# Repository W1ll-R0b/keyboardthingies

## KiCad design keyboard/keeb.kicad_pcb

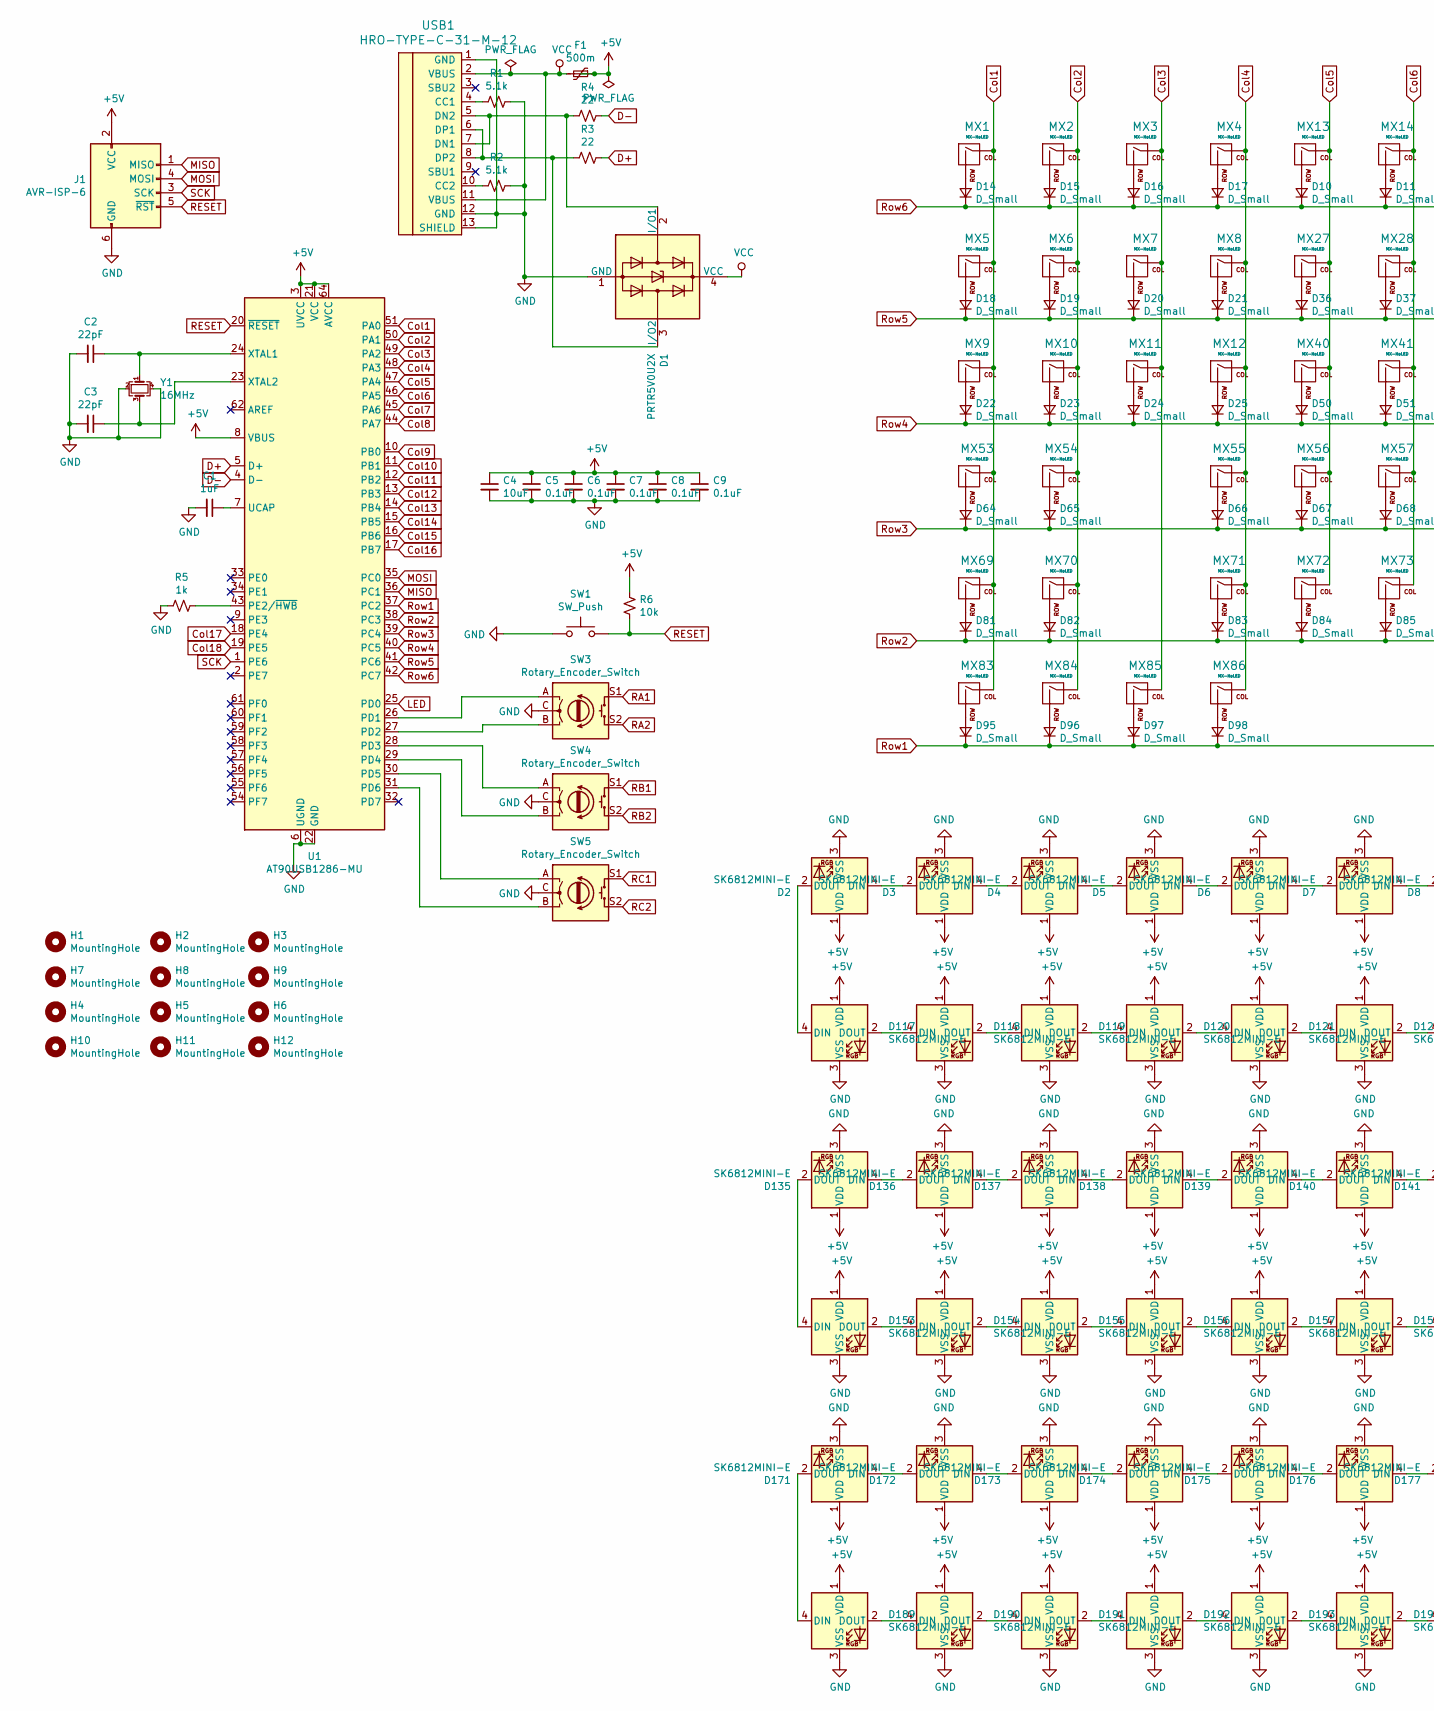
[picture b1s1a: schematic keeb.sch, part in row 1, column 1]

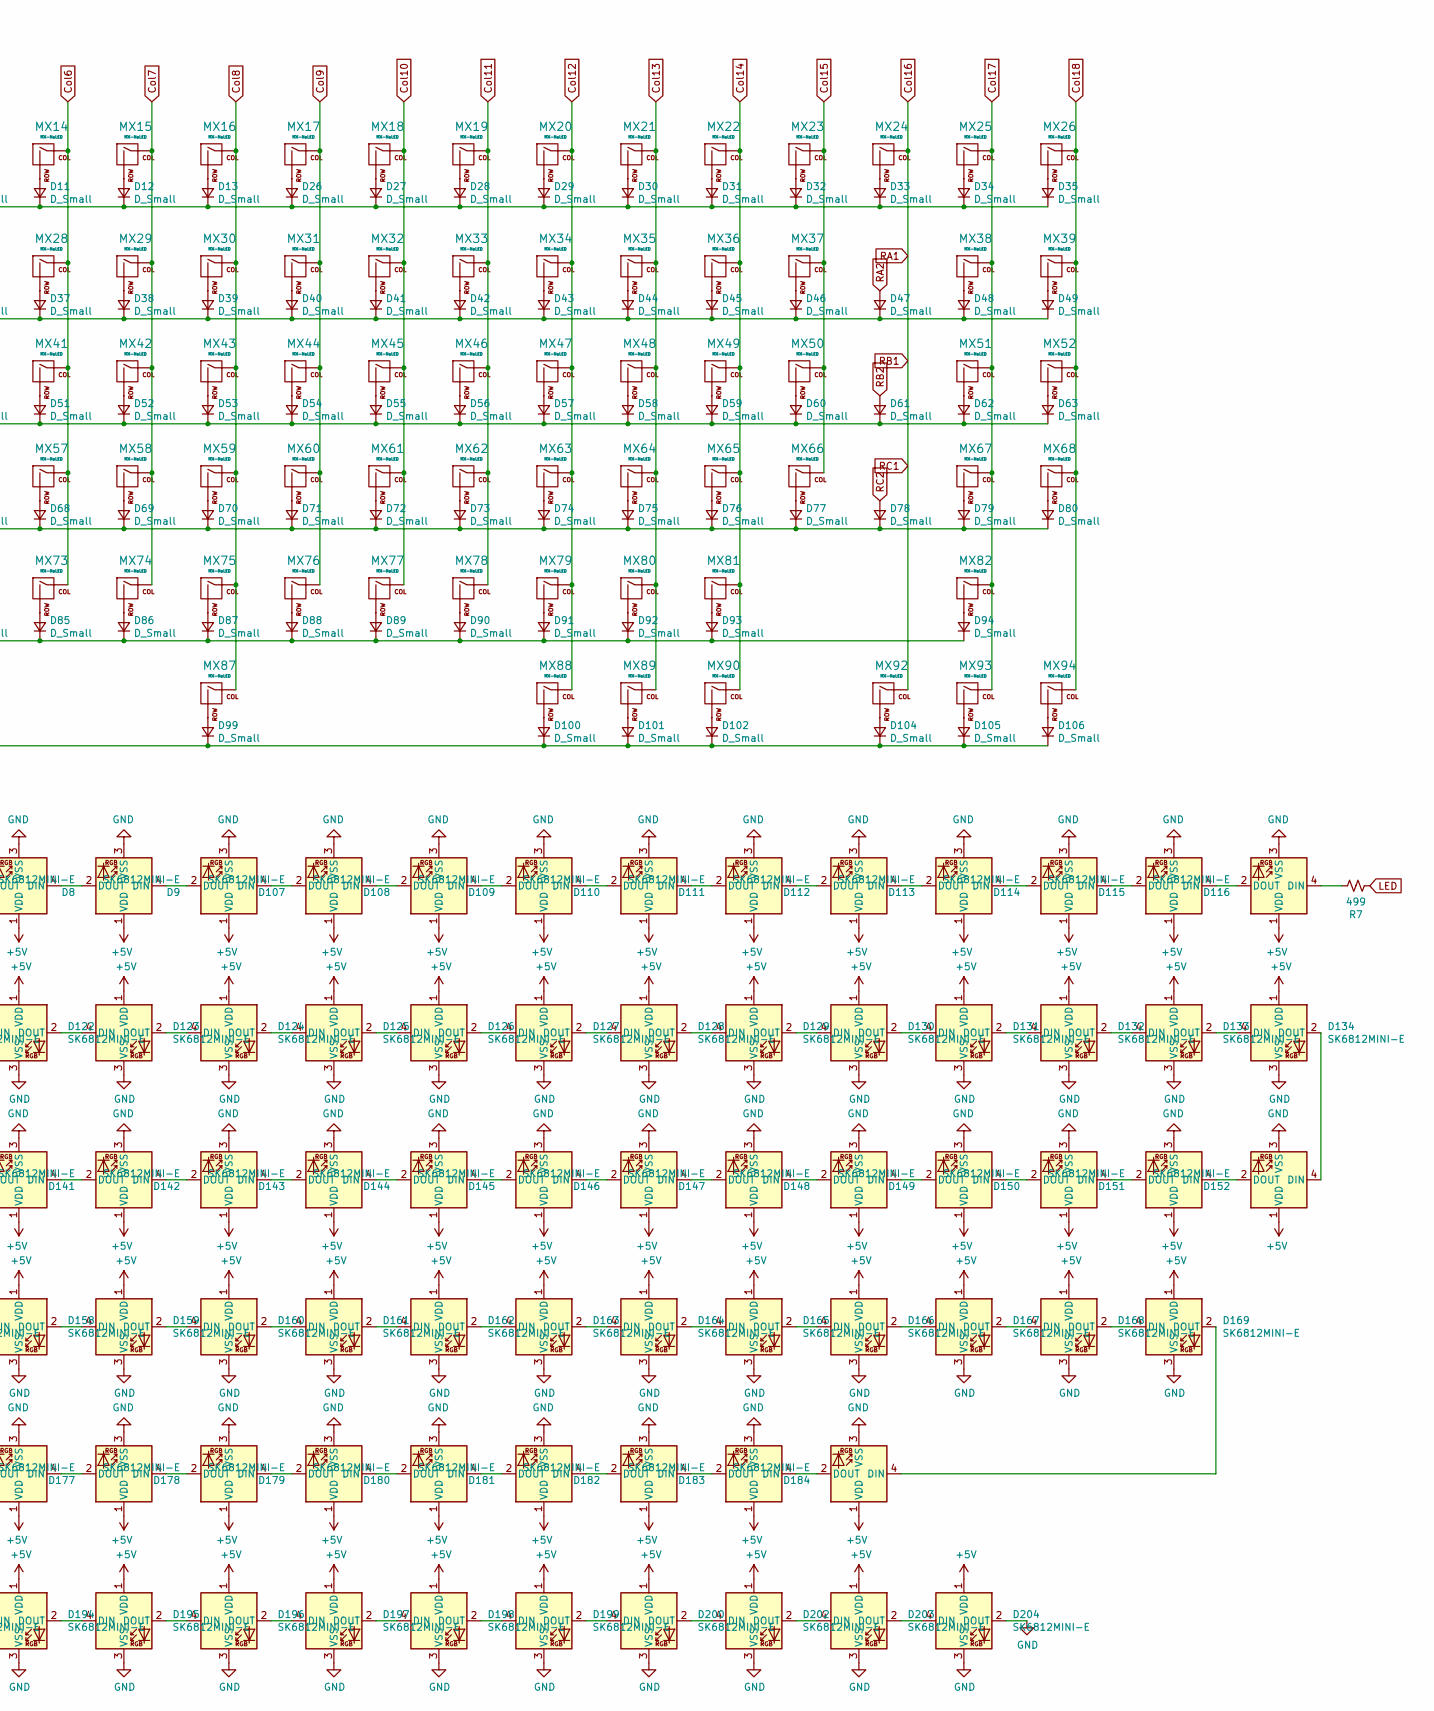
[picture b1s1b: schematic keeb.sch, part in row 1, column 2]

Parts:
C1: 1uF; C_0805_2012Metric
C2, C3: 22pF; C_0805_2012Metric
C4: 10uF; C_0805_2012Metric
C5, C6, C7, C8, C9: 0.1uF; C_0805_2012Metric
D1: PRTR5V0U2X; SOT-143
D2, D3, D4, D5, D6, D7, D8, D9, D107, D108, D109, D110, D111, D112, D113, D114, D115, D116, D117, D118, D119, D120, D121, D122, D123, D124, D125, D126, D127, D128, D129, D130, D131, D132, D133, D134, D135, D136, D137, D138, D139, D140, D141, D142, D143, D144, D145, D146, D147, D148, D149, D150, D151, D152, D153, D154, D155, D156, D157, D158, D159, D160, D161, D162, D163, D164, D165, D166, D167, D168, D169, D171, D172, D173, D174, D175, D176, D177, D178, D179, D180, D181, D182, D183, D184, D189, D190, D191, D192, D193, D194, D195, D196, D197, D198, D199, D200, D202, D203, D204: SK6812MINI-E; MX_SK6812MINI-E
D10, D11, D12, D13, D14, D15, D16, D17, D18, D19, D20, D21, D22, D23, D24, D25, D26, D27, D28, D29, D30, D31, D32, D33, D34, D35, D36, D37, D38, D39, D40, D41, D42, D43, D44, D45, D46, D47, D48, D49, D50, D51, D52, D53, D54, D55, D56, D57, D58, D59, D60, D61, D62, D63, D64, D65, D66, D67, D68, D69, D70, D71, D72, D73, D74, D75, D76, D77, D78, D79, D80, D81, D82, D83, D84, D85, D86, D87, D88, D89, D90, D91, D92, D93, D94, D95, D96, D97, D98, D99, D100, D101, D102, D104, D105, D106: D_Small; D_SOD-123
F1: 500m; Fuse_1206_3216Metric_Pad1.42x1.75mm_HandSolder
H1, H2, H3, H4, H5, H6, H7, H8, H9, H10, H11, H12: MountingHole; MountingHole_2.2mm_M2_DIN965_Pad
J1: AVR-ISP-6; Reset_Pretty-Mask
MX1, MX2, MX3, MX4, MX5, MX6, MX7, MX8, MX9, MX11, MX12, MX13, MX14, MX15, MX16, MX17, MX18, MX19, MX20, MX21, MX22, MX23, MX24, MX25, MX26, MX27, MX28, MX29, MX30, MX31, MX32, MX33, MX34, MX35, MX36, MX38, MX39, MX40, MX41, MX42, MX43, MX44, MX45, MX46, MX47, MX48, MX49, MX51, MX52, MX53, MX55, MX56, MX57, MX58, MX59, MX60, MX61, MX62, MX63, MX64, MX65, MX67, MX68, MX69, MX71, MX72, MX73, MX74, MX75, MX76, MX77, MX78, MX79, MX80, MX82, MX83, MX92, MX93, MX94: MX-NoLED; MXOnly-1U-NoLED
MX10, MX50: MX-NoLED; MXOnly-1.5U-NoLED
MX37: MX-NoLED; MXOnly-2U-NoLED
MX54: MX-NoLED; MXOnly-1.75U-NoLED
MX66, MX70: MX-NoLED; MXOnly-2.25U-NoLED
MX81: MX-NoLED; MXOnly-2.75U-NoLED
MX84, MX85, MX86, MX88, MX89, MX90: MX-NoLED; MXOnly-1.25U-NoLED
MX87: MX-NoLED; MXOnly-6.25U-NoLED
R1, R2: 5.1k; R_0805_2012Metric
R3, R4: 22; R_0805_2012Metric
R5: 1k; R_0805_2012Metric
R6: 10k; R_0805_2012Metric
R7: 499; R_0805_2012Metric
SW1: SW_Push; SKQG-1155865
SW3, SW4, SW5: Rotary_Encoder_Switch; RotaryEncoder_Alps_EC11E-Switch_Vertical_H20mm
U1: AT90USB1286-MU; QFN-64-1EP_9x9mm_P0.5mm_EP7.5x7.5mm
USB1: HRO-TYPE-C-31-M-12; HRO-TYPE-C-31-M-12-HandSoldering
Y1: 16MHz; Crystal_SMD_3225-4Pin_3.2x2.5mm

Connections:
+5V: C4.1, C5.1, C6.1, C7.1, C8.1, C9.1, D2.1 (VDD), D3.1 (VDD), D4.1 (VDD), D5.1 (VDD), D6.1 (VDD), D7.1 (VDD), D8.1 (VDD), D9.1 (VDD), D107.1 (VDD), D108.1 (VDD), D109.1 (VDD), D110.1 (VDD), D111.1 (VDD), D112.1 (VDD), D113.1 (VDD), D114.1 (VDD), D115.1 (VDD), D116.1 (VDD), D117.1 (VDD), D118.1 (VDD), D119.1 (VDD), D120.1 (VDD), D121.1 (VDD), D122.1 (VDD), D123.1 (VDD), D124.1 (VDD), D125.1 (VDD), D126.1 (VDD), D127.1 (VDD), D128.1 (VDD), D129.1 (VDD), D130.1 (VDD), D131.1 (VDD), D132.1 (VDD), D133.1 (VDD), D134.1 (VDD), D135.1 (VDD), D136.1 (VDD), D137.1 (VDD), D138.1 (VDD), D139.1 (VDD), D140.1 (VDD), D141.1 (VDD), D142.1 (VDD), D143.1 (VDD), D144.1 (VDD), D145.1 (VDD), D146.1 (VDD), D147.1 (VDD), D148.1 (VDD), D149.1 (VDD), D150.1 (VDD), D151.1 (VDD), D152.1 (VDD), D153.1 (VDD), D154.1 (VDD), D155.1 (VDD), D156.1 (VDD), D157.1 (VDD), D158.1 (VDD), D159.1 (VDD), D160.1 (VDD), D161.1 (VDD), D162.1 (VDD), D163.1 (VDD), D164.1 (VDD), D165.1 (VDD), D166.1 (VDD), D167.1 (VDD), D168.1 (VDD), D169.1 (VDD), D171.1 (VDD), D172.1 (VDD), D173.1 (VDD), D174.1 (VDD), D175.1 (VDD), D176.1 (VDD), D177.1 (VDD), D178.1 (VDD), D179.1 (VDD), D180.1 (VDD), D181.1 (VDD), D182.1 (VDD), D183.1 (VDD), D184.1 (VDD), D189.1 (VDD), D190.1 (VDD), D191.1 (VDD), D192.1 (VDD), D193.1 (VDD), D194.1 (VDD), D195.1 (VDD), D196.1 (VDD), D197.1 (VDD), D198.1 (VDD), D199.1 (VDD), D200.1 (VDD), D202.1 (VDD), D203.1 (VDD), D204.1 (VDD), F1.1, J1.2 (VCC), R6.1, U1.3 (UVCC), U1.8 (VBUS), U1.21 (VCC), U1.52 (VCC), U1.64 (AVCC)
Col1: MX1.1 (COL), MX5.1 (COL), MX9.1 (COL), MX53.1 (COL), MX69.1 (COL), MX83.1 (COL), U1.51 (PA0)
Col2: MX2.1 (COL), MX6.1 (COL), MX10.1 (COL), MX54.1 (COL), MX70.1 (COL), MX84.1 (COL), U1.50 (PA1)
Col3: MX3.1 (COL), MX7.1 (COL), MX11.1 (COL), MX85.1 (COL), U1.49 (PA2)
Col4: MX4.1 (COL), MX8.1 (COL), MX12.1 (COL), MX55.1 (COL), MX71.1 (COL), MX86.1 (COL), U1.48 (PA3)
Col5: MX13.1 (COL), MX27.1 (COL), MX40.1 (COL), MX56.1 (COL), MX72.1 (COL), U1.47 (PA4)
Col6: MX14.1 (COL), MX28.1 (COL), MX41.1 (COL), MX57.1 (COL), MX73.1 (COL), U1.46 (PA5)
Col7: MX15.1 (COL), MX29.1 (COL), MX42.1 (COL), MX58.1 (COL), MX74.1 (COL), U1.45 (PA6)
Col8: MX16.1 (COL), MX30.1 (COL), MX43.1 (COL), MX59.1 (COL), MX75.1 (COL), MX87.1 (COL), U1.44 (PA7)
Col9: MX17.1 (COL), MX31.1 (COL), MX44.1 (COL), MX60.1 (COL), MX76.1 (COL), U1.10 (PB0)
Col10: MX18.1 (COL), MX32.1 (COL), MX45.1 (COL), MX61.1 (COL), MX77.1 (COL), U1.11 (PB1)
Col11: MX19.1 (COL), MX33.1 (COL), MX46.1 (COL), MX62.1 (COL), MX78.1 (COL), U1.12 (PB2)
Col12: MX20.1 (COL), MX34.1 (COL), MX47.1 (COL), MX63.1 (COL), MX79.1 (COL), MX88.1 (COL), U1.13 (PB3)
Col13: MX21.1 (COL), MX35.1 (COL), MX48.1 (COL), MX64.1 (COL), MX80.1 (COL), MX89.1 (COL), U1.14 (PB4)
Col14: MX22.1 (COL), MX36.1 (COL), MX49.1 (COL), MX65.1 (COL), MX81.1 (COL), MX90.1 (COL), U1.15 (PB5)
Col15: MX23.1 (COL), MX37.1 (COL), MX50.1 (COL), MX66.1 (COL), U1.16 (PB6)
Col16: MX24.1 (COL), MX92.1 (COL), SW3.S1, SW4.S1, SW5.S1, U1.17 (PB7)
Col17: MX25.1 (COL), MX38.1 (COL), MX51.1 (COL), MX67.1 (COL), MX82.1 (COL), MX93.1 (COL), U1.18 (PE4)
Col18: MX26.1 (COL), MX39.1 (COL), MX52.1 (COL), MX68.1 (COL), MX94.1 (COL), U1.19 (PE5)
D+: R3.1, U1.5 (D+)
D-: R4.1, U1.4 (D-)
GND: C1.2, C2.2, C3.2, C4.2, C5.2, C6.2, C7.2, C8.2, C9.2, D1.1 (GND), D2.3 (VSS), D3.3 (VSS), D4.3 (VSS), D5.3 (VSS), D6.3 (VSS), D7.3 (VSS), D8.3 (VSS), D9.3 (VSS), D107.3 (VSS), D108.3 (VSS), D109.3 (VSS), D110.3 (VSS), D111.3 (VSS), D112.3 (VSS), D113.3 (VSS), D114.3 (VSS), D115.3 (VSS), D116.3 (VSS), D117.3 (VSS), D118.3 (VSS), D119.3 (VSS), D120.3 (VSS), D121.3 (VSS), D122.3 (VSS), D123.3 (VSS), D124.3 (VSS), D125.3 (VSS), D126.3 (VSS), D127.3 (VSS), D128.3 (VSS), D129.3 (VSS), D130.3 (VSS), D131.3 (VSS), D132.3 (VSS), D133.3 (VSS), D134.3 (VSS), D135.3 (VSS), D136.3 (VSS), D137.3 (VSS), D138.3 (VSS), D139.3 (VSS), D140.3 (VSS), D141.3 (VSS), D142.3 (VSS), D143.3 (VSS), D144.3 (VSS), D145.3 (VSS), D146.3 (VSS), D147.3 (VSS), D148.3 (VSS), D149.3 (VSS), D150.3 (VSS), D151.3 (VSS), D152.3 (VSS), D153.3 (VSS), D154.3 (VSS), D155.3 (VSS), D156.3 (VSS), D157.3 (VSS), D158.3 (VSS), D159.3 (VSS), D160.3 (VSS), D161.3 (VSS), D162.3 (VSS), D163.3 (VSS), D164.3 (VSS), D165.3 (VSS), D166.3 (VSS), D167.3 (VSS), D168.3 (VSS), D169.3 (VSS), D171.3 (VSS), D172.3 (VSS), D173.3 (VSS), D174.3 (VSS), D175.3 (VSS), D176.3 (VSS), D177.3 (VSS), D178.3 (VSS), D179.3 (VSS), D180.3 (VSS), D181.3 (VSS), D182.3 (VSS), D183.3 (VSS), D184.3 (VSS), D189.3 (VSS), D190.3 (VSS), D191.3 (VSS), D192.3 (VSS), D193.3 (VSS), D194.3 (VSS), D195.3 (VSS), D196.3 (VSS), D197.3 (VSS), D198.3 (VSS), D199.3 (VSS), D200.3 (VSS), D202.3 (VSS), D203.3 (VSS), D204.2 (DOUT), D204.3 (VSS), H1.1, H2.1, H3.1, H4.1, H5.1, H6.1, H7.1, H8.1, H9.1, H10.1, H11.1, H12.1, J1.6 (GND), R1.1, R2.1, R5.2, SW1.1, SW3.C, SW4.C, SW5.C, U1.6 (UGND), U1.22 (GND), U1.53 (GND), U1.63 (GND), U1.65 (GND), USB1.1 (GND), USB1.12 (GND), USB1.13 (SHIELD), Y1.2, Y1.4
LED: R7.2, U1.25 (PD0)
MISO: J1.1 (MISO), U1.36 (PC1)
MOSI: J1.4 (MOSI), U1.35 (PC0)
unnamed: C1.1, U1.7 (UCAP)
unnamed: C2.1, U1.24 (XTAL1), Y1.1
unnamed: C3.1, U1.23 (XTAL2), Y1.3
unnamed: D1.2 (I/O1), R4.2, USB1.5 (DN2), USB1.7 (DN1)
unnamed: D1.3 (I/O2), R3.2, USB1.6 (DP1), USB1.8 (DP2)
unnamed: D2.4 (DIN), D3.2 (DOUT)
unnamed: D3.4 (DIN), D4.2 (DOUT)
unnamed: D4.4 (DIN), D5.2 (DOUT)
unnamed: D5.4 (DIN), D6.2 (DOUT)
unnamed: D6.4 (DIN), D7.2 (DOUT)
unnamed: D7.4 (DIN), D8.2 (DOUT)
unnamed: D8.4 (DIN), D9.2 (DOUT)
unnamed: D10.2 (A), MX13.2 (ROW)
unnamed: D11.2 (A), MX14.2 (ROW)
unnamed: D12.2 (A), MX15.2 (ROW)
unnamed: D13.2 (A), MX16.2 (ROW)
unnamed: D14.2 (A), MX1.2 (ROW)
unnamed: D15.2 (A), MX2.2 (ROW)
unnamed: D16.2 (A), MX3.2 (ROW)
unnamed: D17.2 (A), MX4.2 (ROW)
unnamed: D18.2 (A), MX5.2 (ROW)
unnamed: D19.2 (A), MX6.2 (ROW)
unnamed: D20.2 (A), MX7.2 (ROW)
unnamed: D21.2 (A), MX8.2 (ROW)
unnamed: D22.2 (A), MX9.2 (ROW)
unnamed: D23.2 (A), MX10.2 (ROW)
unnamed: D24.2 (A), MX11.2 (ROW)
unnamed: D25.2 (A), MX12.2 (ROW)
unnamed: D26.2 (A), MX17.2 (ROW)
unnamed: D27.2 (A), MX18.2 (ROW)
unnamed: D28.2 (A), MX19.2 (ROW)
unnamed: D29.2 (A), MX20.2 (ROW)
unnamed: D30.2 (A), MX21.2 (ROW)
unnamed: D31.2 (A), MX22.2 (ROW)
unnamed: D32.2 (A), MX23.2 (ROW)
unnamed: D33.2 (A), MX24.2 (ROW)
unnamed: D34.2 (A), MX25.2 (ROW)
unnamed: D35.2 (A), MX26.2 (ROW)
unnamed: D36.2 (A), MX27.2 (ROW)
unnamed: D37.2 (A), MX28.2 (ROW)
unnamed: D38.2 (A), MX29.2 (ROW)
unnamed: D39.2 (A), MX30.2 (ROW)
unnamed: D40.2 (A), MX31.2 (ROW)
unnamed: D41.2 (A), MX32.2 (ROW)
unnamed: D42.2 (A), MX33.2 (ROW)
unnamed: D43.2 (A), MX34.2 (ROW)
unnamed: D44.2 (A), MX35.2 (ROW)
unnamed: D45.2 (A), MX36.2 (ROW)
unnamed: D46.2 (A), MX37.2 (ROW)
unnamed: D48.2 (A), MX38.2 (ROW)
unnamed: D49.2 (A), MX39.2 (ROW)
unnamed: D50.2 (A), MX40.2 (ROW)
unnamed: D51.2 (A), MX41.2 (ROW)
unnamed: D52.2 (A), MX42.2 (ROW)
unnamed: D53.2 (A), MX43.2 (ROW)
unnamed: D54.2 (A), MX44.2 (ROW)
unnamed: D55.2 (A), MX45.2 (ROW)
unnamed: D56.2 (A), MX46.2 (ROW)
unnamed: D57.2 (A), MX47.2 (ROW)
unnamed: D58.2 (A), MX48.2 (ROW)
unnamed: D59.2 (A), MX49.2 (ROW)
unnamed: D60.2 (A), MX50.2 (ROW)
unnamed: D62.2 (A), MX51.2 (ROW)
unnamed: D63.2 (A), MX52.2 (ROW)
unnamed: D64.2 (A), MX53.2 (ROW)
unnamed: D65.2 (A), MX54.2 (ROW)
unnamed: D66.2 (A), MX55.2 (ROW)
unnamed: D67.2 (A), MX56.2 (ROW)
unnamed: D68.2 (A), MX57.2 (ROW)
unnamed: D69.2 (A), MX58.2 (ROW)
unnamed: D70.2 (A), MX59.2 (ROW)
unnamed: D71.2 (A), MX60.2 (ROW)
unnamed: D72.2 (A), MX61.2 (ROW)
unnamed: D73.2 (A), MX62.2 (ROW)
unnamed: D74.2 (A), MX63.2 (ROW)
unnamed: D75.2 (A), MX64.2 (ROW)
unnamed: D76.2 (A), MX65.2 (ROW)
unnamed: D77.2 (A), MX66.2 (ROW)
unnamed: D79.2 (A), MX67.2 (ROW)
unnamed: D80.2 (A), MX68.2 (ROW)
unnamed: D81.2 (A), MX69.2 (ROW)
unnamed: D82.2 (A), MX70.2 (ROW)
unnamed: D83.2 (A), MX71.2 (ROW)
unnamed: D84.2 (A), MX72.2 (ROW)
unnamed: D85.2 (A), MX73.2 (ROW)
unnamed: D86.2 (A), MX74.2 (ROW)
unnamed: D87.2 (A), MX75.2 (ROW)
unnamed: D88.2 (A), MX76.2 (ROW)
unnamed: D89.2 (A), MX77.2 (ROW)
unnamed: D90.2 (A), MX78.2 (ROW)
unnamed: D91.2 (A), MX79.2 (ROW)
unnamed: D92.2 (A), MX80.2 (ROW)
unnamed: D93.2 (A), MX81.2 (ROW)
unnamed: D94.2 (A), MX82.2 (ROW)
unnamed: D95.2 (A), MX83.2 (ROW)
unnamed: D96.2 (A), MX84.2 (ROW)
unnamed: D97.2 (A), MX85.2 (ROW)
unnamed: D98.2 (A), MX86.2 (ROW)
unnamed: D99.2 (A), MX87.2 (ROW)
unnamed: D100.2 (A), MX88.2 (ROW)
unnamed: D101.2 (A), MX89.2 (ROW)
unnamed: D102.2 (A), MX90.2 (ROW)
unnamed: D104.2 (A), MX92.2 (ROW)
unnamed: D105.2 (A), MX93.2 (ROW)
unnamed: D106.2 (A), MX94.2 (ROW)
unnamed: D9.4 (DIN), D107.2 (DOUT)
unnamed: D107.4 (DIN), D108.2 (DOUT)
unnamed: D108.4 (DIN), D109.2 (DOUT)
unnamed: D109.4 (DIN), D110.2 (DOUT)
unnamed: D110.4 (DIN), D111.2 (DOUT)
unnamed: D111.4 (DIN), D112.2 (DOUT)
unnamed: D112.4 (DIN), D113.2 (DOUT)
unnamed: D113.4 (DIN), D114.2 (DOUT)
unnamed: D114.4 (DIN), D115.2 (DOUT)
unnamed: D115.4 (DIN), D116.2 (DOUT)
unnamed: D116.4 (DIN), R7.1
unnamed: D117.2 (DOUT), D118.4 (DIN)
unnamed: D2.2 (DOUT), D117.4 (DIN)
unnamed: D118.2 (DOUT), D119.4 (DIN)
unnamed: D119.2 (DOUT), D120.4 (DIN)
unnamed: D120.2 (DOUT), D121.4 (DIN)
unnamed: D121.2 (DOUT), D122.4 (DIN)
unnamed: D122.2 (DOUT), D123.4 (DIN)
unnamed: D123.2 (DOUT), D124.4 (DIN)
unnamed: D124.2 (DOUT), D125.4 (DIN)
unnamed: D125.2 (DOUT), D126.4 (DIN)
unnamed: D126.2 (DOUT), D127.4 (DIN)
unnamed: D127.2 (DOUT), D128.4 (DIN)
unnamed: D128.2 (DOUT), D129.4 (DIN)
unnamed: D129.2 (DOUT), D130.4 (DIN)
unnamed: D130.2 (DOUT), D131.4 (DIN)
unnamed: D131.2 (DOUT), D132.4 (DIN)
unnamed: D132.2 (DOUT), D133.4 (DIN)
unnamed: D133.2 (DOUT), D134.4 (DIN)
unnamed: D134.2 (DOUT), D152.4 (DIN)
unnamed: D135.2 (DOUT), D153.4 (DIN)
unnamed: D135.4 (DIN), D136.2 (DOUT)
unnamed: D136.4 (DIN), D137.2 (DOUT)
unnamed: D137.4 (DIN), D138.2 (DOUT)
unnamed: D138.4 (DIN), D139.2 (DOUT)
unnamed: D139.4 (DIN), D140.2 (DOUT)
unnamed: D140.4 (DIN), D141.2 (DOUT)
unnamed: D141.4 (DIN), D142.2 (DOUT)
unnamed: D142.4 (DIN), D143.2 (DOUT)
unnamed: D143.4 (DIN), D144.2 (DOUT)
unnamed: D144.4 (DIN), D145.2 (DOUT)
unnamed: D145.4 (DIN), D146.2 (DOUT)
unnamed: D146.4 (DIN), D147.2 (DOUT)
unnamed: D147.4 (DIN), D148.2 (DOUT)
unnamed: D148.4 (DIN), D149.2 (DOUT)
unnamed: D149.4 (DIN), D150.2 (DOUT)
unnamed: D150.4 (DIN), D151.2 (DOUT)
unnamed: D151.4 (DIN), D152.2 (DOUT)
unnamed: D153.2 (DOUT), D154.4 (DIN)
unnamed: D154.2 (DOUT), D155.4 (DIN)
unnamed: D155.2 (DOUT), D156.4 (DIN)
unnamed: D156.2 (DOUT), D157.4 (DIN)
unnamed: D157.2 (DOUT), D158.4 (DIN)
unnamed: D158.2 (DOUT), D159.4 (DIN)
unnamed: D159.2 (DOUT), D160.4 (DIN)
unnamed: D160.2 (DOUT), D161.4 (DIN)
unnamed: D161.2 (DOUT), D162.4 (DIN)
unnamed: D162.2 (DOUT), D163.4 (DIN)
unnamed: D163.2 (DOUT), D164.4 (DIN)
unnamed: D164.2 (DOUT), D165.4 (DIN)
unnamed: D165.2 (DOUT), D166.4 (DIN)
unnamed: D166.2 (DOUT), D167.4 (DIN)
unnamed: D167.2 (DOUT), D168.4 (DIN)
unnamed: D168.2 (DOUT), D169.4 (DIN)
unnamed: D169.2 (DOUT), D184.4 (DIN)
unnamed: D171.2 (DOUT), D189.4 (DIN)
unnamed: D171.4 (DIN), D172.2 (DOUT)
unnamed: D172.4 (DIN), D173.2 (DOUT)
unnamed: D173.4 (DIN), D174.2 (DOUT)
unnamed: D174.4 (DIN), D175.2 (DOUT)
unnamed: D175.4 (DIN), D176.2 (DOUT)
unnamed: D176.4 (DIN), D177.2 (DOUT)
unnamed: D177.4 (DIN), D178.2 (DOUT)
unnamed: D178.4 (DIN), D179.2 (DOUT)
unnamed: D179.4 (DIN), D180.2 (DOUT)
unnamed: D180.4 (DIN), D181.2 (DOUT)
unnamed: D181.4 (DIN), D182.2 (DOUT)
unnamed: D182.4 (DIN), D183.2 (DOUT)
unnamed: D183.4 (DIN), D184.2 (DOUT)
unnamed: D189.2 (DOUT), D190.4 (DIN)
unnamed: D190.2 (DOUT), D191.4 (DIN)
unnamed: D191.2 (DOUT), D192.4 (DIN)
unnamed: D192.2 (DOUT), D193.4 (DIN)
unnamed: D193.2 (DOUT), D194.4 (DIN)
unnamed: D194.2 (DOUT), D195.4 (DIN)
unnamed: D195.2 (DOUT), D196.4 (DIN)
unnamed: D196.2 (DOUT), D197.4 (DIN)
unnamed: D197.2 (DOUT), D198.4 (DIN)
unnamed: D198.2 (DOUT), D199.4 (DIN)
unnamed: D199.2 (DOUT), D200.4 (DIN)
unnamed: D200.2 (DOUT), D202.4 (DIN)
unnamed: D202.2 (DOUT), D203.4 (DIN)
unnamed: D203.2 (DOUT), D204.4 (DIN)
unnamed: R1.2, USB1.4 (CC1)
unnamed: R2.2, USB1.10 (CC2)
unnamed: R5.1, U1.43 (PE2/~HWB)
unnamed: SW3.A, U1.26 (PD1)
unnamed: SW3.B, U1.27 (PD2)
unnamed: SW4.A, U1.28 (PD3)
unnamed: SW4.B, U1.29 (PD4)
unnamed: SW5.A, U1.30 (PD5)
unnamed: SW5.B, U1.31 (PD6)
RA2: D47.2 (A), SW3.S2
RB2: D61.2 (A), SW4.S2
RC2: D78.2 (A), SW5.S2
RESET: J1.5 (~RST), R6.2, SW1.2, U1.20 (~RESET)
Row1: D95.1 (K), D96.1 (K), D97.1 (K), D98.1 (K), D99.1 (K), D100.1 (K), D101.1 (K), D102.1 (K), D104.1 (K), D105.1 (K), D106.1 (K), U1.37 (PC2)
Row2: D81.1 (K), D82.1 (K), D83.1 (K), D84.1 (K), D85.1 (K), D86.1 (K), D87.1 (K), D88.1 (K), D89.1 (K), D90.1 (K), D91.1 (K), D92.1 (K), D93.1 (K), D94.1 (K), U1.38 (PC3)
Row3: D64.1 (K), D65.1 (K), D66.1 (K), D67.1 (K), D68.1 (K), D69.1 (K), D70.1 (K), D71.1 (K), D72.1 (K), D73.1 (K), D74.1 (K), D75.1 (K), D76.1 (K), D77.1 (K), D78.1 (K), D79.1 (K), D80.1 (K), U1.39 (PC4)
Row4: D22.1 (K), D23.1 (K), D24.1 (K), D25.1 (K), D50.1 (K), D51.1 (K), D52.1 (K), D53.1 (K), D54.1 (K), D55.1 (K), D56.1 (K), D57.1 (K), D58.1 (K), D59.1 (K), D60.1 (K), D61.1 (K), D62.1 (K), D63.1 (K), U1.40 (PC5)
Row5: D18.1 (K), D19.1 (K), D20.1 (K), D21.1 (K), D36.1 (K), D37.1 (K), D38.1 (K), D39.1 (K), D40.1 (K), D41.1 (K), D42.1 (K), D43.1 (K), D44.1 (K), D45.1 (K), D46.1 (K), D47.1 (K), D48.1 (K), D49.1 (K), U1.41 (PC6)
Row6: D10.1 (K), D11.1 (K), D12.1 (K), D13.1 (K), D14.1 (K), D15.1 (K), D16.1 (K), D17.1 (K), D26.1 (K), D27.1 (K), D28.1 (K), D29.1 (K), D30.1 (K), D31.1 (K), D32.1 (K), D33.1 (K), D34.1 (K), D35.1 (K), U1.42 (PC7)
SCK: J1.3 (SCK), U1.1 (PE6)
VCC: D1.4 (VCC), F1.2, USB1.2 (VBUS), USB1.11 (VBUS)

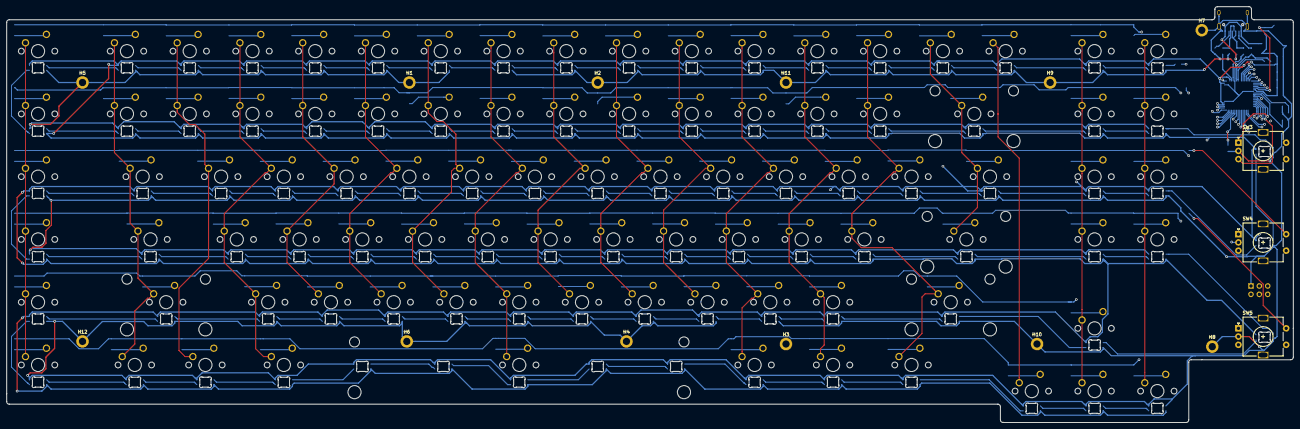
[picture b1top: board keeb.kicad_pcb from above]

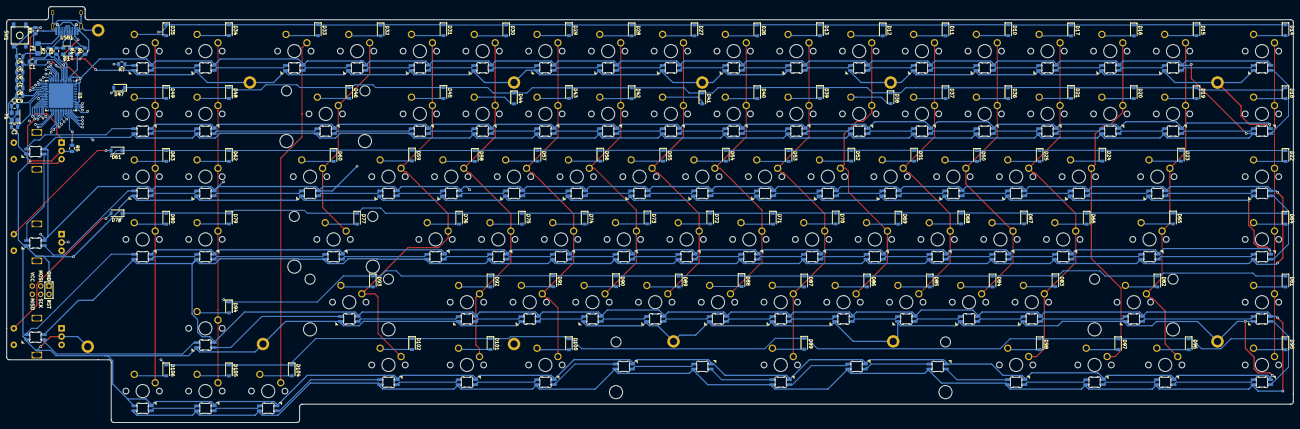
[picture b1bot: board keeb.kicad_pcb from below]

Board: 4 copper layers, 390.5 x 126.2 mm, 327 parts (119 on the bottom side), 244 nets.

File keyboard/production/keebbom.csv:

Comment,Designator,Footprint,LCSC
1uF,C1,Capacitor_SMD:C_0805_2012Metric,C28323
22pF,"C2,C3",Capacitor_SMD:C_0805_2012Metric,C1804
10uF,C4,Capacitor_SMD:C_0805_2012Metric,C15850
0.1uF,"C5,C6,C7,C8,C9",Capacitor_SMD:C_0805_2012Metric,C49678
PRTR5V0U2X,D1,Package_TO_SOT_SMD:SOT-143,C2827688
D_Small,"D10,D11,D12,D13,D14,D15,D16,D17,D18,D19,D20,D21,D22,D23,D24,D25,D26,D27,D28,D29,D30,D31,D32,D33,D34,D35,D36,D37,D38,D39,D40,D41,D42,D43,D44,D45,D46,D47,D48,D49,D50,D51,D52,D53,D54,D55,D56,D57,D58,D59,D60,D61,D62,D63,D64,D65,D66,D67,D68,D69,D70,D71,D72,D73,D74,D75,D76,D77,D78,D79,D80,D81,D82,D83,D84,D85,D86,D87,D88,D89,D90,D91,D92,D93,D94,D95,D96,D97,D98,D99,D100,D101,D102,D104,D105,D106",Diode_SMD:D_SOD-123,C725478
SK6812MINI-E,"D2,D3,D4,D5,D6,D7,D8,D9,D107,D108,D109,D110,D111,D112,D113,D114,D115,D116,D117,D118,D119,D120,D121,D122,D123,D124,D125,D126,D127,D128,D129,D130,D131,D132,D133,D134,D135,D136,D137,D138,D139,D140,D141,D142,D143,D144,D145,D146,D147,D148,D149,D150,D151,D152,D153,D154,D155,D156,D157,D158,D159,D160,D161,D162,D163,D164,D165,D166,D167,D168,D169,D171,D172,D173,D174,D175,D176,D177,D178,D179,D180,D181,D182,D183,D184,D189,D190,D191,D192,D193,D194,D195,D196,D197,D198,D199,D200,D202,D203,D204",kicad-keyboard-parts:MX_SK6812MINI-E,C5378731
500m,F1,Fuse:Fuse_1206_3216Metric_Pad1.42x1.75mm_HandSolder,C455450
5.1k,"R1,R2",Resistor_SMD:R_0805_2012Metric,C27834
22,"R3,R4",Resistor_SMD:R_0805_2012Metric,C17561
1k,R5,Resistor_SMD:R_0805_2012Metric,C17513
10k,R6,Resistor_SMD:R_0805_2012Metric,C17414
499,R7,Resistor_SMD:R_0805_2012Metric,C130458
SW_Push,SW1,random-keyboard-parts:SKQG-1155865,C115351
AT90USB1286-MU,U1,Package_DFN_QFN:QFN-64-1EP_9x9mm_P0.5mm_EP7.5x7.5mm,C614573
HRO-TYPE-C-31-M-12,USB1,Type-C:HRO-TYPE-C-31-M-12-HandSoldering,C165948
16MHz,Y1,Crystal:Crystal_SMD_3225-4Pin_3.2x2.5mm,C127500

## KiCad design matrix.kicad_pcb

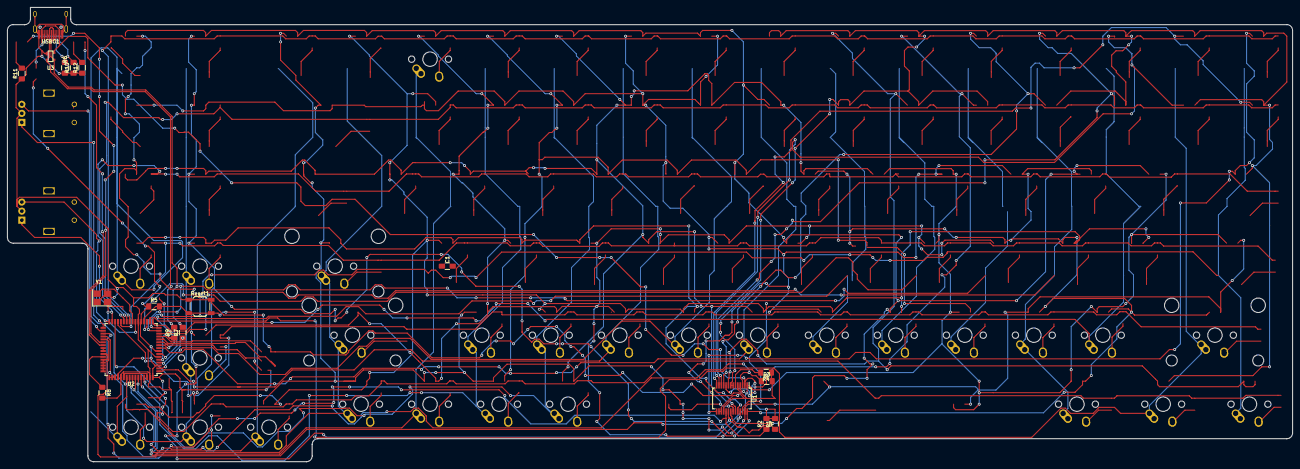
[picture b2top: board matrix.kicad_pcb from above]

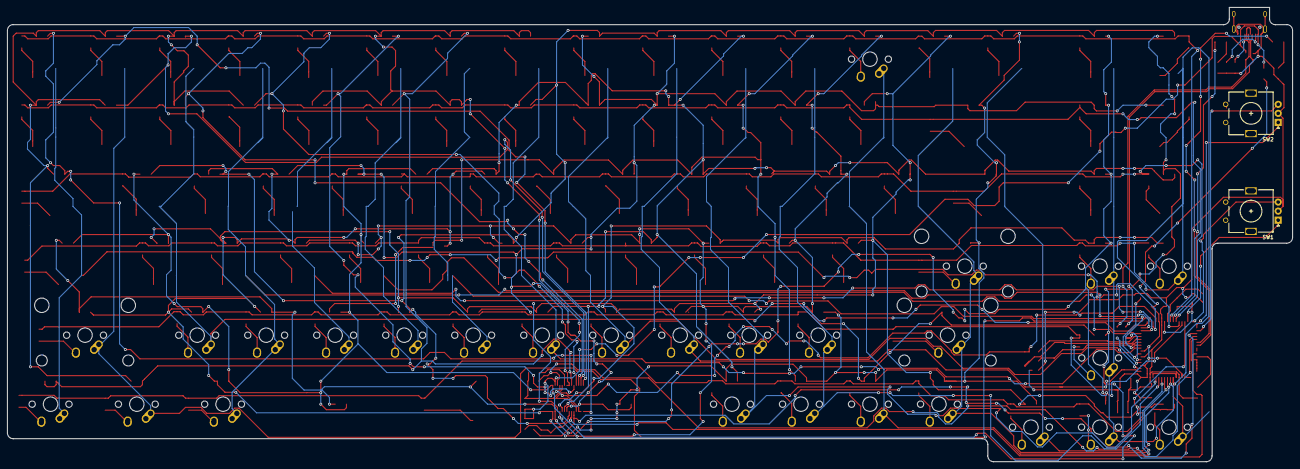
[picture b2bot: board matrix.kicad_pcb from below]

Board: 2 copper layers, 354.8 x 125.4 mm, 48 parts (30 on the bottom side), 39 nets.

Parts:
MX13: F12; MX-1U-NoLED
MX61: '; MX-1U-NoLED
MX62: ENTR; MX-2.25U-NoLED
MX63: PGDN; MX-1U-NoLED
MX64: MCRO4; MX-1U-NoLED
MX65: SHIFTL; MX-2.25U-NoLED
MX66: Z; MX-1U-NoLED
MX67: X; MX-1U-NoLED
MX68: C; MX-1U-NoLED
MX69: V; MX-1U-NoLED
MX70: B; MX-1U-NoLED
MX71: N; MX-1U-NoLED
MX72: M; MX-1U-NoLED
MX73: ,<; MX-1U-NoLED
MX74: .>; MX-1U-NoLED
MX75: /?; MX-1U-NoLED
MX76: SHIFTR; MX-2.75U-NoLED
MX77: UP; MX-1U-NoLED
MX78: CTRLL; MX-1.25U-NoLED
MX79: WIN; MX-1.25U-NoLED
MX80: ALTL; MX-1.25U-NoLED
MX82: ALTR; MX-1U-NoLED
MX83: MENU; MX-1U-NoLED
MX84: FN; MX-1U-NoLED
MX85: CTRLR; MX-1U-NoLED
MX86: LEFT; MX-1U-NoLED
MX87: DOWN; MX-1U-NoLED
MX88: RIGHT; MX-1U-NoLED
R1, R2: 4k7; R_1206_3216Metric_Pad1.42x1.75mm_HandSolder
R3: 100k; R_1206_3216Metric_Pad1.42x1.75mm_HandSolder
R4: 20k; R_1206_3216Metric_Pad1.42x1.75mm_HandSolder
R5: 10k; R_1206_3216Metric_Pad1.42x1.75mm_HandSolder
R6, R10: 5.1k; R_1206_3216Metric_Pad1.42x1.75mm_HandSolder
R7, R9: 22; R_1206_3216Metric_Pad1.42x1.75mm_HandSolder
R8: 1k; R_1206_3216Metric_Pad1.42x1.75mm_HandSolder
R11, R12: 470; R_1206_3216Metric_Pad1.42x1.75mm_HandSolder
Reset1: SW_Push; SW_SPST_SKQG_WithStem
SW1, SW2: Rotary_Encoder; RotaryEncoder_Alps_EC11E_Vertical_H20mm
U1: IS31FL3731-SA; SSOP-28_5.3x10.2mm_P0.65mm
U2: AT90USB1286-AU; TQFP-64_14x14mm_P0.8mm
U3: PRTR5V0U2X; SOT143B
USBC1: HRO-TYPE-C-31-M-12; HRO-TYPE-C-31-M-12-HandSoldering
Y1: 16MHz; Crystal_SMD_3225-4Pin_3.2x2.5mm_HandSoldering

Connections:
+5V: R5.1, U2.3, U2.8, U2.21, U2.52, U2.64
AD: MX61.2, R3.2, R4.1, R6.1, R8.2, R10.1, R11.1, R12.1, Reset1.1, SW1.C, SW2.C, U1.5, U1.18, U2.6, U2.22, U2.53, U2.63, U3.1, USBC1.1, USBC1.12, USBC1.13, Y1.1, Y1.3
CB1: U1.7, U1.8
COL0: MX78.1, U2.19
COL1: MX65.1, MX79.1, U2.18
COL2: MX66.1, U2.17
COL3: MX67.1, MX80.1, U2.16
COL4: MX68.1, U2.15
COL5: MX69.1, U2.14
COL6: MX70.1, U2.10
COL7: MX71.1, U2.9
COL8: MX72.1, U2.2
COL9: MX73.1, U2.1
COL10: MX74.1, MX82.1, U2.61
COL11: MX75.1, MX83.1, U2.60
COL12: MX13.1, MX84.1, U2.59
COL13: MX62.1, MX76.1, MX85.1, U2.58
COL14: MX86.1, U2.57
COL15: MX63.1, MX77.1, MX87.1, U2.56
COL16: MX64.1, MX88.1, U2.55
D+: R9.1, U2.5
D-: R7.1, U2.4
DN: R7.2, U3.3, USBC1.5, USBC1.7
DP: R9.2, U3.2, USBC1.6, USBC1.8
unnamed: R6.2, USBC1.4
unnamed: R8.1, U2.43
unnamed: R10.2, USBC1.10
R00: SW1.A, U2.31
R01: SW1.B, U2.32
R10: SW2.A, U2.33
R11: SW2.B, U2.34
RESET: R5.2, Reset1.2, U2.20
REXT: R4.2, U1.6
SCL: R1.1, U1.20, U2.37
SDA: R2.1, U1.19, U2.35
SDB: R3.1, U1.3, U2.36
VCC: MX61.1, R1.2, R2.2, U1.2, U3.4, USBC1.2, USBC1.11
XTAL1: U2.24, Y1.4
XTAL2: U2.23, Y1.2

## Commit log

2023-11-02 begin
2023-11-02 addsubby
2023-11-02 subbyupdate
2023-11-02 setup
2023-11-03 prematrix
2023-11-03 corefix
2023-11-03 typecadd
2023-11-04 schematicfootprintless
2023-11-04 schematicupdate
2023-11-04 annotatedkeyschematic
2023-11-04 maybefinishedschematic
2023-11-04 footprints
2023-11-07 ithinkdoneschematic
2023-11-08 nocapschematic
2023-11-11 frfrfinishedschematic
    I promise this time
2023-11-13 prerouting+finalnewdoneschematicIswear
2023-12-21 routing progress
2023-12-22 routingcontinue
2024-03-18 fgvdfuhjkh (final i think)
2024-03-18 final attempt
2024-03-20 restart1
2024-03-20 restart1.1
2024-03-20 restart1.2
2024-03-20 restart1.3
2024-03-20 restart1.4
2024-04-03 FinalFinal
2024-04-03 FullKeebSchematic
2024-04-03 KeebSchWithLayout
2024-04-09 keeb-routed
2024-04-09 keeb-fillzones
2024-05-03 It works
    Works ╰(*°▽°*)╯
